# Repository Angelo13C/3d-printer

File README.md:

# 3D printer

https://github.com/user-attachments/assets/5a46b2cb-1782-422b-acf3-2e04f320dc16

I have designed and built a CoreXY 3D printer (all the aspects of the machine: the firmware, a control interface to communicate with the firmware, the electronics and the mechanics). And I've decided to make everything open source!

This is a table of contents:

| Name  | Description |
| ------------- | ------------- |
| [Firmware](firmware)  | The software running on the printer, written in Rust  |
| [Electronics](electronics)  | The electrical board on which the firmware runs, designed in KiCad  |
| Mechanics | The mechanical structure of the printer, designed in Fusion360 (I have not made these files open source yet) |
| [Control interface](control-interface) | An app used to communicate with the firmware of the printer from a desktop computer |

## How it works
[Here I've made a simplified explanation of how a 3D printer works](HOW_A_3D_PRINTER_WORKS.md).

## Contributions
I would be really glad if you could give me some tips on how to improve this project (make a pull request!)

_By the way, I am not a native English speaker. I am sorry if there is any grammar error 😅_

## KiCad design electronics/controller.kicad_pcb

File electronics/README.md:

# Electronics
This is the electrical control board on which the firmware runs.

The board receives stable `24V` from an external power supply unit and requires around `16A` of current at peak, but during almost all of the time it requires around `10A`
of current (because the heaters are not fully on after having reached the target temperature).

On the board there's a switching regulator that converts the `24V` to `5V`, which is used by the `endstops`, the `BLTouch` and by the linear regulator
that instead converts the `5V` to `3.3V` which is used by the [ESP32-S3-WROOM-1](https://www.espressif.com/sites/default/files/documentation/esp32-s3-wroom-1_wroom-1u_datasheet_en.pdf)
microcontroller, the [MT29F2G01ABAGDWB-IT](https://datasheet.lcsc.com/lcsc/1912111437_Micron-Tech-MT29F2G01ABAGDWB-IT-G_C410863.pdf) NAND flash memory.

## Schematic
This is the electrical schematic of the board:

## PCB
The PCB has 4 layers (PWR/SIGNAL, GND, GND, PWR/SIGNAL), this is an image of the top layer:

## Possible improvements
Some ideas for further improvement are:
- Add some little LEDs on the board to show that the power rails are good.
- Use an external Sigma-Delta ADC to improve the accuracy of the temperatures' readings (or calibrate the microcontroller's internal ADC).
- Put the antenna area of the ESP32 on the border of the PCB, to improve the antenna's performance.
- Change some connectors.

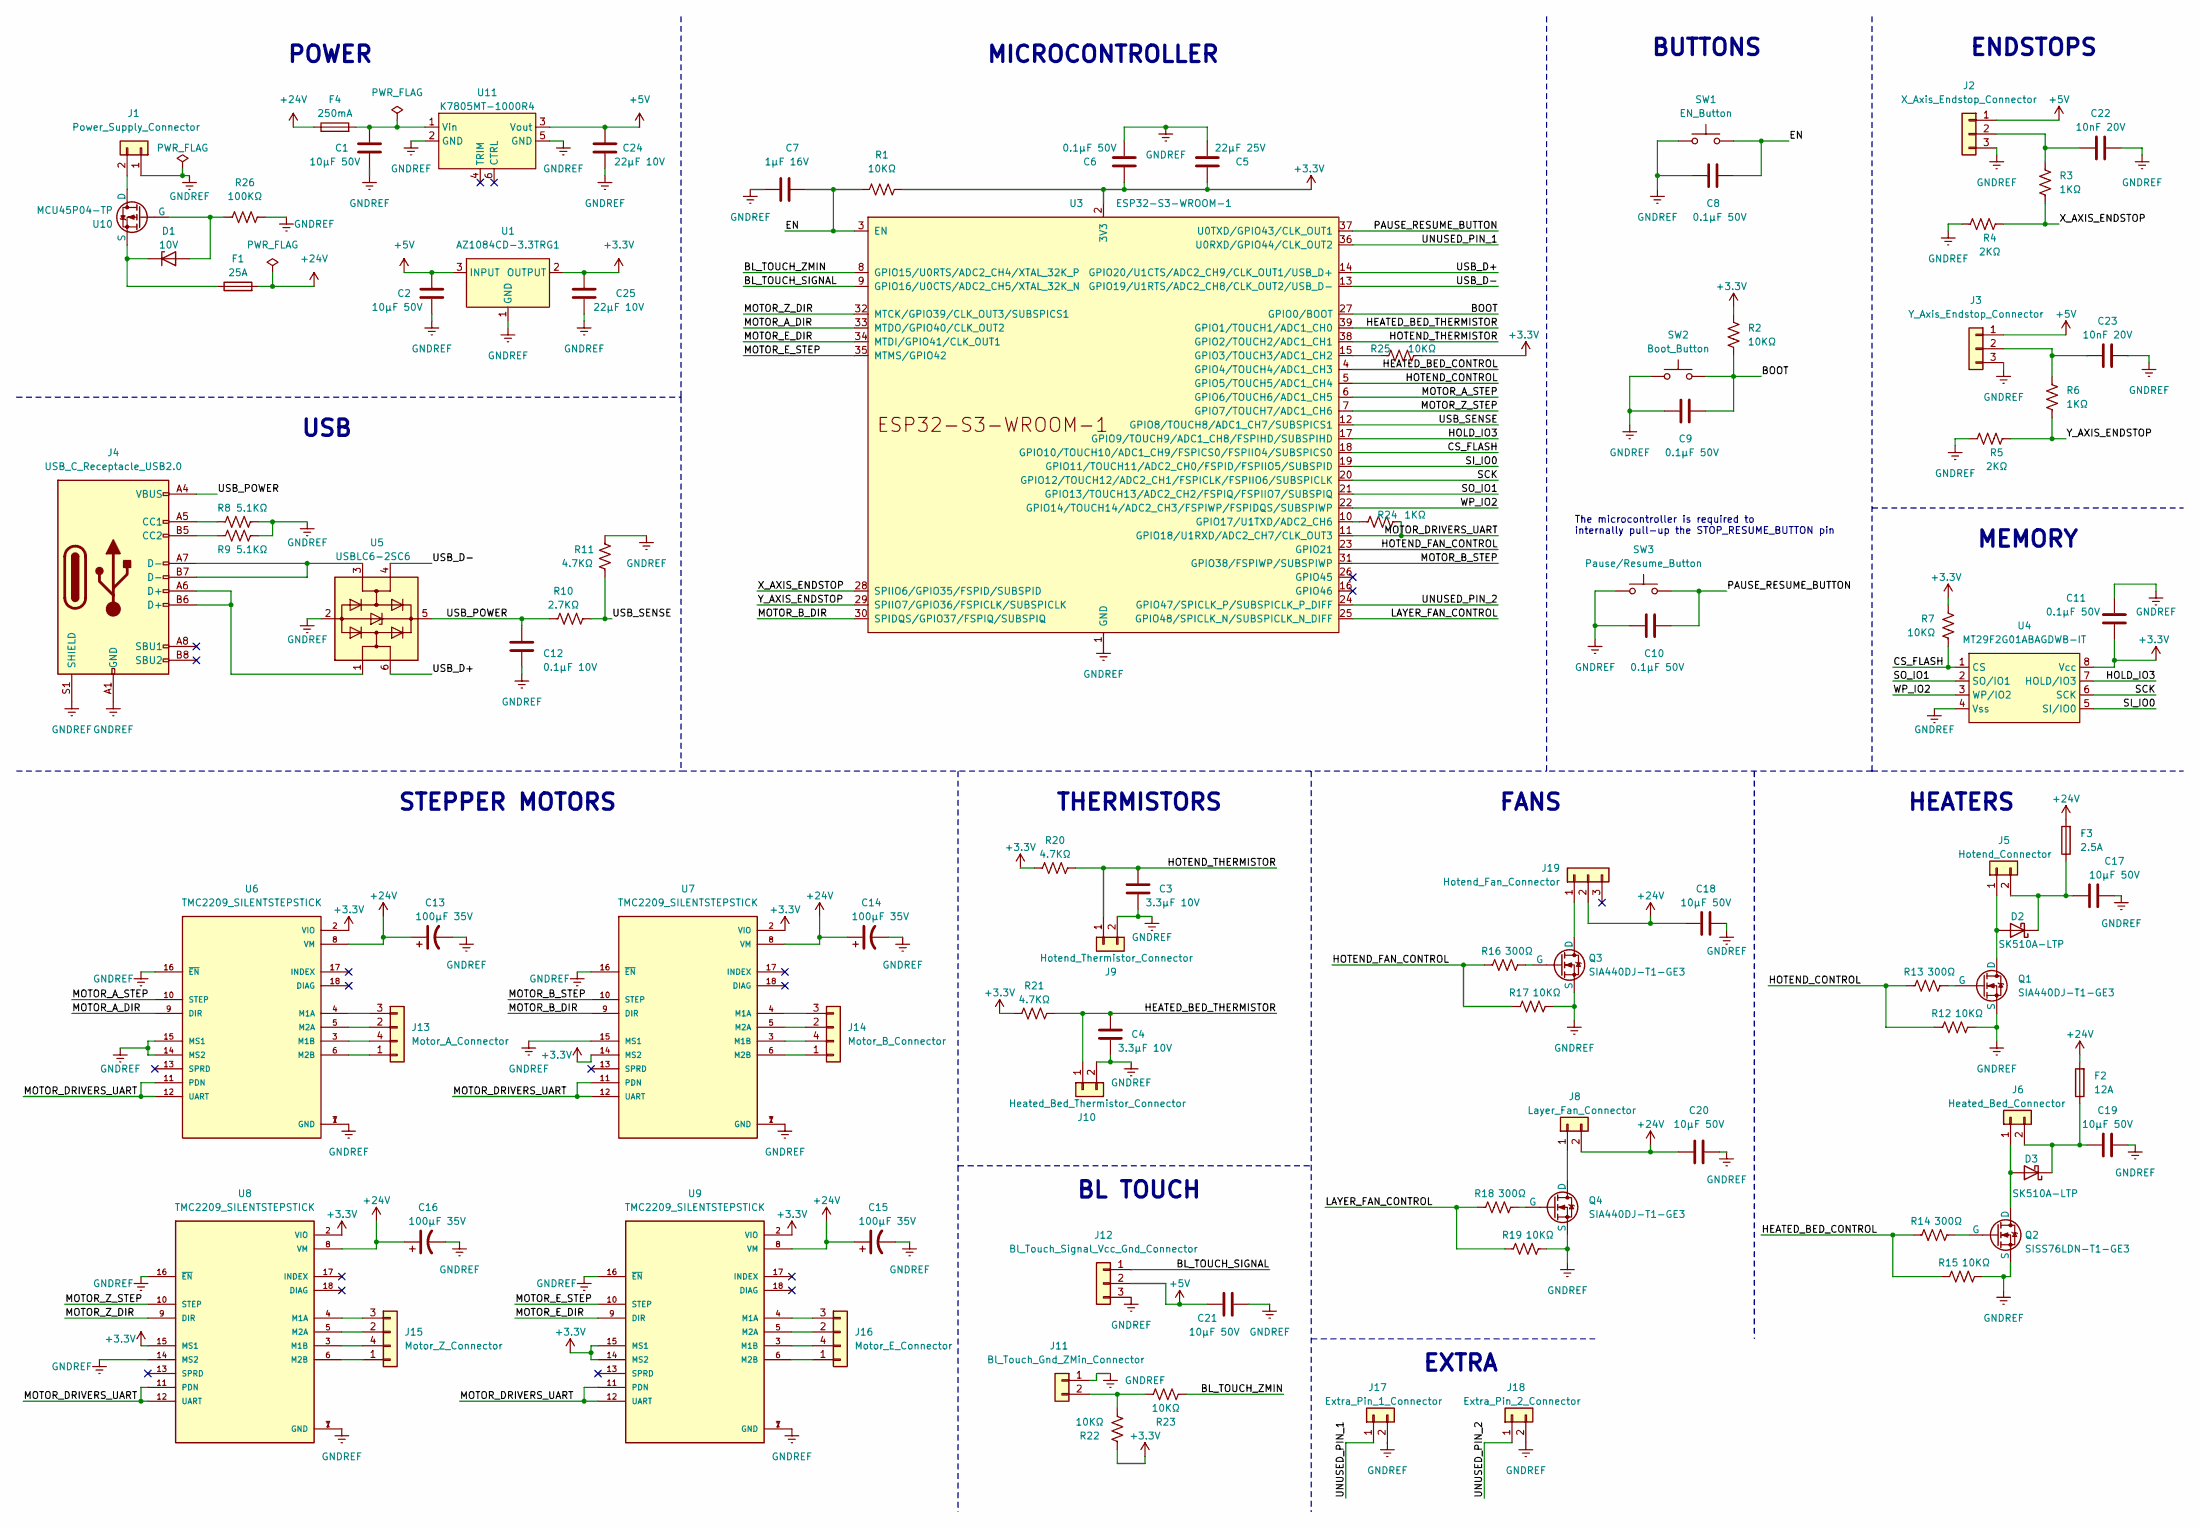
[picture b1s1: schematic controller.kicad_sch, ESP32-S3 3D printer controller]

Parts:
C1, C2, C17, C18, C19, C20, C21: 10µF 50V; C_1206_3216Metric_Pad1.33x1.80mm_HandSolder
C3, C4: 3.3µF 10V; C_1206_3216Metric_Pad1.33x1.80mm_HandSolder
C5: 22µF 25V; C_1206_3216Metric_Pad1.33x1.80mm_HandSolder
C6, C8, C9, C10, C11: 0.1µF 50V; C_1206_3216Metric_Pad1.33x1.80mm_HandSolder
C7: 1µF 16V; C_1206_3216Metric_Pad1.33x1.80mm_HandSolder
C12: 0.1µF 10V; C_1206_3216Metric_Pad1.33x1.80mm_HandSolder
C13, C14, C15, C16: 100µF 35V; CP_Radial_D6.3mm_P2.50mm
C22, C23: 10nF 20V; C_1206_3216Metric_Pad1.33x1.80mm_HandSolder
C24, C25: 22µF 10V; C_1206_3216Metric_Pad1.33x1.80mm_HandSolder
D1: 10V; D_SOD-123
D2, D3: SK510A-LTP; SMADO-214AC_LEAD-FRAME_MCC-L
F1: 25A; Fuse_1206_3216Metric_Pad1.42x1.75mm_HandSolder
F2: 12A; Fuse_1206_3216Metric_Pad1.42x1.75mm_HandSolder
F3: 2.5A; Fuse_1206_3216Metric_Pad1.42x1.75mm_HandSolder
F4: 250mA; Fuse_1206_3216Metric_Pad1.42x1.75mm_HandSolder
J1: Power_Supply_Connector; TerminalBlock_Phoenix_MKDS-1,5-2-5.08_1x02_P5.08mm_Horizont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
J2: X_Axis_Endstop_Connector; PinHeader_1x03_P2.54mm_Vertical
J3: Y_Axis_Endstop_Connector; PinHeader_1x03_P2.54mm_Vertical
J4: USB_C_Receptacle_USB2.0; USB_C_Receptacle_GCT_USB4105-xx-A_16P_TopMnt_Horizontal
J5: Hotend_Connector; SolderWire-0.5sqmm_1x02_P4.6mm_D0.9mm_OD2.1mm
J6: Heated_Bed_Connector; SolderWire-2.5sqmm_1x02_P7.2mm_D2.4mm_OD3.6mm
J8: Layer_Fan_Connector; SolderWire-0.5sqmm_1x02_P4.6mm_D0.9mm_OD2.1mm
J9: Hotend_Thermistor_Connector; JST_XH_B2B-XH-A_1x02_P2.50mm_Vertical
J10: Heated_Bed_Thermistor_Connector; JST_XH_B2B-XH-A_1x02_P2.50mm_Vertical
J11: Bl_Touch_Gnd_ZMin_Connector; PinHeader_1x02_P2.54mm_Vertical
J12: Bl_Touch_Signal_Vcc_Gnd_Connector; PinHeader_1x03_P2.54mm_Vertical
J13: Motor_A_Connector; JST_XH_B4B-XH-A_1x04_P2.50mm_Vertical
J14: Motor_B_Connector; JST_XH_B4B-XH-A_1x04_P2.50mm_Vertical
J15: Motor_Z_Connector; JST_XH_B4B-XH-A_1x04_P2.50mm_Vertical
J16: Motor_E_Connector; JST_XH_B4B-XH-A_1x04_P2.50mm_Vertical
J17: Extra_Pin_1_Connector; SolderWire-0.5sqmm_1x02_P4.6mm_D0.9mm_OD2.1mm
J18: Extra_Pin_2_Connector; SolderWire-0.5sqmm_1x02_P4.6mm_D0.9mm_OD2.1mm
J19: Hotend_Fan_Connector; Molex_KK-254_AE-6410-03A_1x03_P2.54mm_Vertical
Q1, Q3, Q4: SIA440DJ-T1-GE3; Vishay_PowerPAK_SC70-6L_Single
Q2: SISS76LDN-T1-GE3; PowerPAK® 1212-8SH
R1, R2, R7, R12, R15, R17, R19, R22, R23, R25: 10KΩ; R_1206_3216Metric_Pad1.30x1.75mm_HandSolder
R3, R6, R24: 1KΩ; R_1206_3216Metric_Pad1.30x1.75mm_HandSolder
R4, R5: 2KΩ; R_1206_3216Metric_Pad1.30x1.75mm_HandSolder
R8, R9: 5.1KΩ; R_1206_3216Metric_Pad1.30x1.75mm_HandSolder
R10: 2.7KΩ; R_1206_3216Metric_Pad1.30x1.75mm_HandSolder
R11, R20, R21: 4.7KΩ; R_1206_3216Metric_Pad1.30x1.75mm_HandSolder
R13, R14, R16, R18: 300Ω; R_1206_3216Metric_Pad1.30x1.75mm_HandSolder
R26: 100KΩ; R_1206_3216Metric_Pad1.30x1.75mm_HandSolder
SW1: EN_Button; SW_PUSH_6mm
SW2: Boot_Button; SW_PUSH_6mm
SW3: Pause/Resume_Button; SolderWire-0.5sqmm_1x02_P4.6mm_D0.9mm_OD2.1mm
U1: AZ1084CD-3.3TRG1; TO-252-3_TabPin2
U3: ESP32-S3-WROOM-1
U4: MT29F2G01ABAGDWB-IT; U-PDFN (MLP8)
U5: USBLC6-2SC6; SOT-23-6
U6, U7, U8, U9: TMC2209_SILENTSTEPSTICK; MODULE_TMC2209_SILENTSTEPSTICK; PARTREV 1.20
U10: MCU45P04-TP; TO-252-3_TabPin2
U11: K7805MT-1000R4; MODULE_6-SMD

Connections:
+3.3V: C5.1, C6.1, C11.1, C25.2, R1.2, R2.2, R7.2, R20.1, R21.1, R22.1, R25.2, U1.2 (OUTPUT), U3.2 (3V3), U4.8 (Vcc), U6.2 (VIO), U7.2 (VIO), U7.14 (MS2), U8.2 (VIO), U8.15 (MS1), U9.2 (VIO), U9.14 (MS2), U9.15 (MS1)
+5V: C2.2, C21.1, C24.2, J2.1, J3.1, J12.2, U1.3 (INPUT), U11.3 (Vout)
+24V: C13.1, C14.1, C15.1, C16.1, C18.2, C20.1, F1.2, F2.2, F3.2, F4.1, J8.2, J19.2, U6.8 (VM), U7.8 (VM), U8.8 (VM), U9.8 (VM)
/BL_TOUCH_SIGNAL: J12.1, U3.9 (GPIO16/U0CTS/ADC2_CH5/XTAL_32K_N)
/BL_TOUCH_ZMIN: R23.1, U3.8 (GPIO15/U0RTS/ADC2_CH4/XTAL_32K_P)
/BOOT: C9.1, R2.1, SW2.2, U3.27 (GPIO0/BOOT); also elsewhere on the board
/CS_FLASH: R7.1, U3.18 (GPIO10/TOUCH10/ADC1_CH9/FSPICS0/FSPIIO4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), U4.1 (CS)
/EN: C7.1, C8.1, R1.1, SW1.2, U3.3 (EN); also elsewhere on the board
/HEATED_BED_CONTROL: R14.1, R15.1, U3.4 (GPIO4/TOUCH4/ADC1_CH3)
/HEATED_BED_THERMISTOR: C4.2, J10.1, R21.2, U3.39 (GPIO1/TOUCH1/ADC1_CH0)
/HOLD_IO3: U3.17 (GPIO9/TOUCH9/ADC1_CH8/FSPIHD/SUBSPIHD), U4.7 (HOLD/IO3)
/HOTEND_CONTROL: R12.1, R13.1, U3.5 (GPIO5/TOUCH5/ADC1_CH4)
/HOTEND_FAN_CONTROL: R16.1, R17.1, U3.23 (GPIO21)
/HOTEND_THERMISTOR: C3.2, J9.1, R20.2, U3.38 (GPIO2/TOUCH2/ADC1_CH1)
/LAYER_FAN_CONTROL: R18.1, R19.1, U3.25 (GPIO48/SPICLK_N/SUBSPICLK_N_DIFF)
/MOTOR_A_DIR: U3.33 (MTDO/GPIO40/CLK_OUT2), U6.9 (DIR)
/MOTOR_A_STEP: U3.6 (GPIO6/TOUCH6/ADC1_CH5), U6.10 (STEP)
/MOTOR_B_DIR: U3.30 (SPIDQS/GPIO37/FSPIQ/SUBSPIQ), U7.9 (DIR)
/MOTOR_B_STEP: U3.31 (GPIO38/FSPIWP/SUBSPIWP), U7.10 (STEP)
/MOTOR_DRIVERS_UART: R24.2, U3.11 (GPIO18/U1RXD/ADC2_CH7/CLK_OUT3), U6.11 (PDN), U6.12 (UART), U7.11 (PDN), U7.12 (UART), U8.11 (PDN), U8.12 (UART), U9.11 (PDN), U9.12 (UART)
/MOTOR_E_DIR: U3.34 (MTDI/GPIO41/CLK_OUT1), U9.9 (DIR)
/MOTOR_E_STEP: U3.35 (MTMS/GPIO42), U9.10 (STEP)
/MOTOR_Z_DIR: U3.32 (MTCK/GPIO39/CLK_OUT3/SUBSPICS1), U8.9 (DIR)
/MOTOR_Z_STEP: U3.7 (GPIO7/TOUCH7/ADC1_CH6), U8.10 (STEP)
/PAUSE_RESUME_BUTTON: C10.1, SW3.2, U3.37 (U0TXD/GPIO43/CLK_OUT1)
/SCK: U3.20 (GPIO12/TOUCH12/ADC2_CH1/FSPICLK/FSPIIO6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), U4.6 (SCK)
/SI_IO0: U3.19 (GPIO11/TOUCH11/ADC2_CH0/FSPID/FSPIIO5/S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), U4.5 (SI/IO0)
/SO_IO1: U3.21 (GPIO13/TOUCH13/ADC2_CH2/FSPIQ/FSPIIO7/S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), U4.2 (SO/IO1)
/UNUSED_PIN_1: J17.1, U3.36 (U0RXD/GPIO44/CLK_OUT2)
/UNUSED_PIN_2: J18.1, U3.24 (GPIO47/SPICLK_P/SUBSPICLK_P_DIFF)
/USB_D+: U3.14 (GPIO20/U1CTS/ADC2_CH9/CLK_OUT1/USB_D+), U5.6 (I/O1)
/USB_D-: U3.13 (GPIO19/U1RTS/ADC2_CH8/CLK_OUT2/USB_D-), U5.4 (I/O2)
/USB_POWER: C12.1, J4.A4 (VBUS), J4.A9 (VBUS), J4.B4 (VBUS), J4.B9 (VBUS), R10.2, U5.5 (VBUS)
/USB_SENSE: R10.1, R11.2, U3.12 (GPIO8/TOUCH8/ADC1_CH7/SUBSPICS1)
/WP_IO2: U3.22 (GPIO14/TOUCH14/ADC2_CH3/FSPIWP/FSPIDQS/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), U4.3 (WP/IO2)
/X_AXIS_ENDSTOP: R3.1, R4.1, U3.28 (SPIIO6/GPIO35/FSPID/SUBSPID)
/Y_AXIS_ENDSTOP: R5.1, R6.1, U3.29 (SPIIO7/GPIO36/FSPICLK/SUBSPICLK)
GNDREF: C1.1, C2.1, C3.1, C4.1, C5.2, C6.2, C7.2, C8.2, C9.2, C10.2, C11.2, C12.2, C13.2, C14.2, C15.2, C16.2, C17.2, C18.1, C19.2, C20.2, C21.2, C22.2, C23.2, C24.1, C25.1, J1.1, J2.3, J3.3, J4.A1 (GND), J4.A12 (GND), J4.B1 (GND), J4.B12 (GND), J4.S1 (SHIELD), J9.2, J10.2, J11.1, J12.3, J17.2, J18.2, Q1.3 (S), Q2.3 (S), Q3.3 (S), Q4.3 (S), R4.2, R5.2, R8.2, R9.2, R11.1, R12.2, R15.2, R17.2, R19.2, R26.2, SW1.1, SW2.1, SW3.1, U1.1 (GND), U3.1 (GND), U3.40 (GND), U3.41 (GND), U4.4 (Vss), U5.2 (GND), U6.1 (GND), U6.7 (GND), U6.14 (MS2), U6.15 (MS1), U6.16 (~EN), U7.1 (GND), U7.7 (GND), U7.15 (MS1), U7.16 (~EN), U8.1 (GND), U8.7 (GND), U8.14 (MS2), U8.16 (~EN), U9.1 (GND), U9.7 (GND), U9.16 (~EN), U11.2 (GND), U11.5 (GND); also elsewhere on the board
unnamed: D1.2 (A), R26.1, U10.1 (G)
unnamed: D1.1 (K), F1.1, U10.3 (S)
unnamed: D2.2 (A), J5.1, Q1.1 (D)
unnamed: C17.1, D2.1 (K), F3.1, J5.2
unnamed: D3.2 (A), J6.1, Q2.1 (D)
unnamed: C19.1, D3.1 (K), F2.1, J6.2
unnamed: J1.2, U10.2 (D)
unnamed: C22.1, J2.2, R3.2
unnamed: C23.1, J3.2, R6.2
unnamed: J4.A5 (CC1), R8.1
unnamed: J4.B5 (CC2), R9.1
unnamed: J4.A6 (D+), J4.B6 (D+), U5.1 (I/O1)
unnamed: J4.A7 (D-), J4.B7 (D-), U5.3 (I/O2)
unnamed: J8.1, Q4.1 (D)
unnamed: J11.2, R22.2, R23.2
unnamed: J13.1, U6.6 (M2B)
unnamed: J13.2, U6.5 (M2A)
unnamed: J13.3, U6.4 (M1A)
unnamed: J13.4, U6.3 (M1B)
unnamed: J14.1, U7.6 (M2B)
unnamed: J14.2, U7.5 (M2A)
unnamed: J14.3, U7.4 (M1A)
unnamed: J14.4, U7.3 (M1B)
unnamed: J15.1, U8.6 (M2B)
unnamed: J15.2, U8.5 (M2A)
unnamed: J15.3, U8.4 (M1A)
unnamed: J15.4, U8.3 (M1B)
unnamed: J16.1, U9.6 (M2B)
unnamed: J16.2, U9.5 (M2A)
unnamed: J16.3, U9.4 (M1A)
unnamed: J16.4, U9.3 (M1B)
unnamed: J19.1, Q3.1 (D)
unnamed: Q1.2 (G), R13.2
unnamed: Q2.2 (G), R14.2
unnamed: Q3.2 (G), R16.2
unnamed: Q4.2 (G), R18.2
unnamed: R25.1, U3.15 (GPIO3/TOUCH3/ADC1_CH2)
unnamed: R24.1, U3.10 (GPIO17/U1TXD/ADC2_CH6)
unnamed: C1.2, F4.2, U11.1 (Vin)

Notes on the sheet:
FANS
BL TOUCH
USB
STEPPER MOTORS
The microcontroller is required to internally pull-up the STOP_RESUME_BUTTON pin
MICROCONTROLLER
EXTRA
ENDSTOPS
HEATERS
BUTTONS
MEMORY
THERMISTORS
POWER

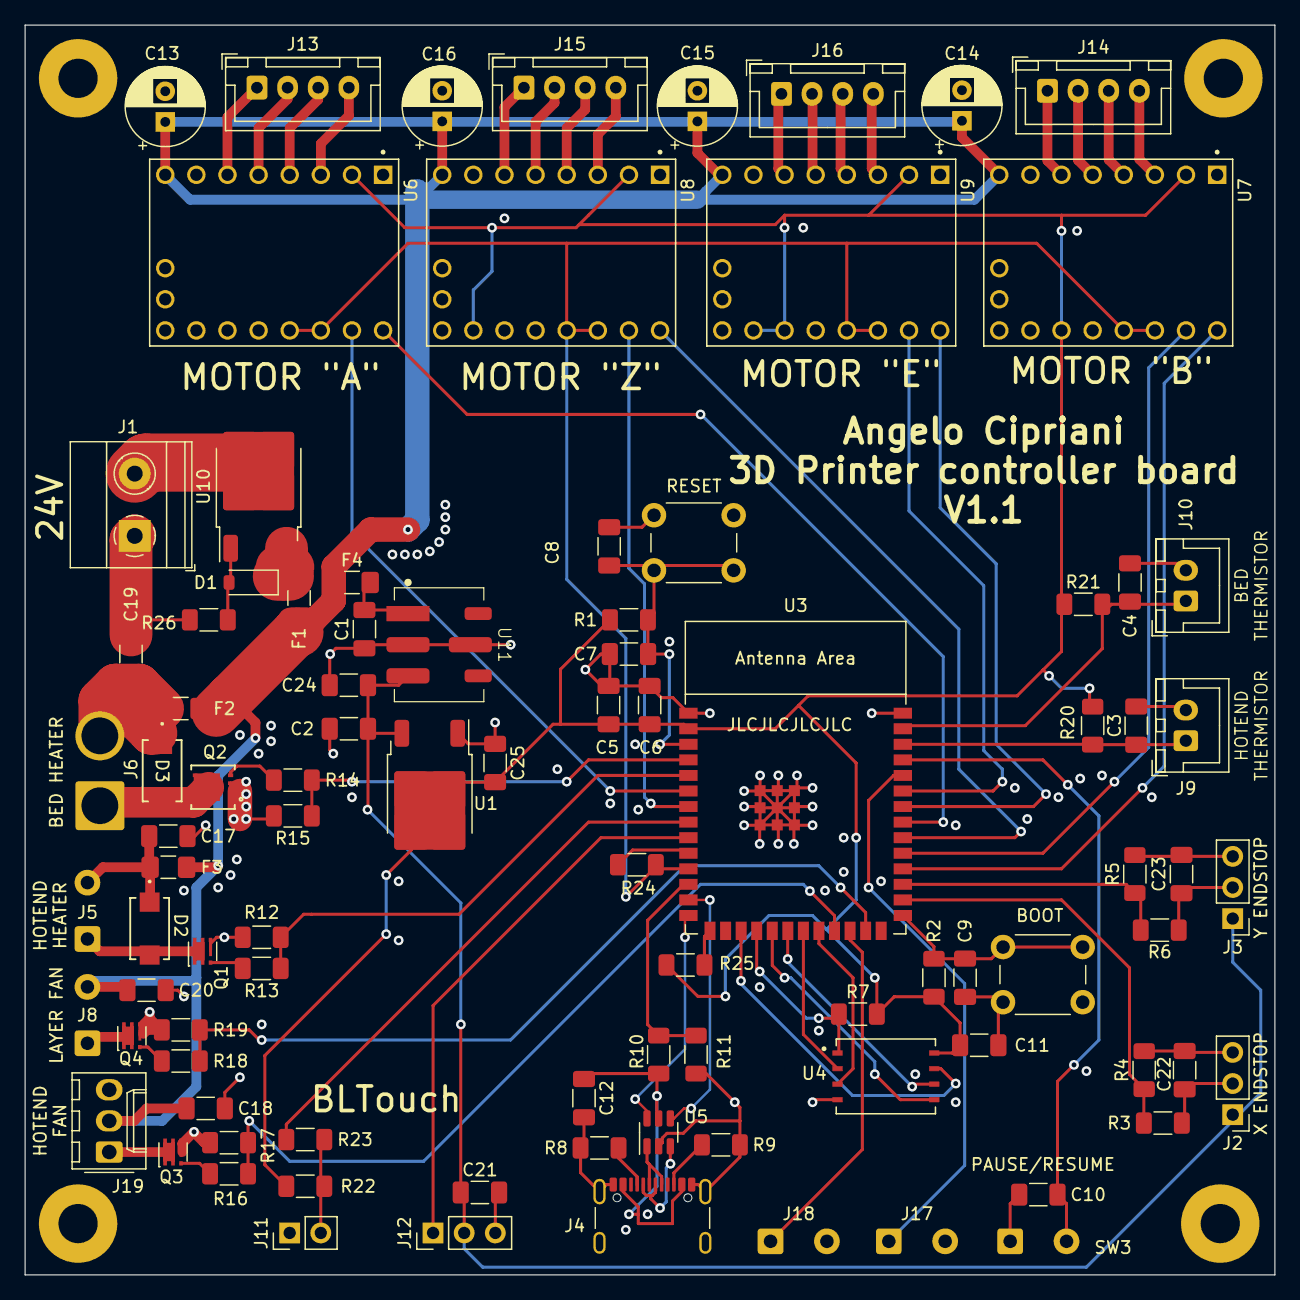
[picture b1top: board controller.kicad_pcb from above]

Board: 4 copper layers, 102.0 x 102.0 mm, 93 parts (0 on the bottom side), 77 nets.

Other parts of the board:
BOOT: Boot_Button; SW_PUSH_6mm
RESET: EN_Button; SW_PUSH_6mm

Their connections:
/BOOT: BOOT.2; also elsewhere on the board
/EN: RESET.2; also elsewhere on the board
GNDREF: BOOT.1, RESET.1; also elsewhere on the board

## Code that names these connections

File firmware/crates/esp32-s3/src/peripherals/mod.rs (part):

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	bed_thermistor_pin: Option<<Self as PeripheralsTrait>::HeatedBedAdcPin>,

	hotend_cartridge_heater_pin: Option<<Self as PeripheralsTrait>::CartridgeHeaterPin>,
	hotend_thermistor_pin: Option<<Self as PeripheralsTrait>::HotendAdcPin>,

	adc: Option<<Self as PeripheralsTrait>::Adc>,

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	type StepperTickerTimer = Timer;
	type Kinematics = CoreXYKinematics;

	type LeftDirPin = PinDriver<'static, Gpio40, Output>;
	type LeftStepPin = PinDriver<'static, Gpio6, Output>;
	type RightDirPin = PinDriver<'static, Gpio37, Output>;
	type RightStepPin = PinDriver<'static, Gpio38, Output>;
	type ZAxisDirPin = PinDriver<'static, Gpio39, Output>;
	type ZAxisStepPin = PinDriver<'static, Gpio7, Output>;
	type ExtruderDirPin = PinDriver<'static, Gpio41, Output>;
	type ExtruderStepPin = PinDriver<'static, Gpio42, Output>;

	type UartDriver = UARTDriver<'static>;

	type XAxisEndstop = Button<InputPin<'static, Gpio35>>;
	type YAxisEndstop = Button<InputPin<'static, Gpio36>>;
	type ZAxisEndstop = BLTouch<LedcPwmPin<'static>, InputPin<'static, Gpio15>>;

	type FlashChip = MT29F2G01ABAGDWB;
	type FlashSpi = SpiSingleDeviceDriver<'static>;
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	type FanPin = LedcPwmPin<'static>;

	type CartridgeHeaterPin = LedcPwmPin<'static>;
	type HotendAdcPin = AdcPin<'static, ADC1, 3, Gpio2>;

	type HeatedBedHeaterPin = LedcPwmPin<'static>;
	type HeatedBedAdcPin = AdcPin<'static, ADC1, 3, Gpio1>;

	type Adc = Adc<'static, ADC1>;

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	type Ota = EspOta;

	#[cfg(feature = "usb")]
	type UsbSensePin = InputPin<'static, Gpio20>;
	#[cfg(feature = "usb")]
	type UsbBus = firmware_core::printer::components::mock::MockUsbBus;

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
	fn take_hotend_thermistor_pin(&mut self) -> Option<Self::HotendAdcPin>
	{
		self.hotend_thermistor_pin.take()
	}

	fn take_adc(&mut self) -> Option<Self::Adc>
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			system_time: Some(SystemTime::new()?),
			uart_driver: Some(UARTDriver(UartDriver::new(
				peripherals.uart1,
				peripherals.pins.gpio18,
				peripherals.pins.gpio17,
				None as Option<Gpio0>,
				None as Option<Gpio0>,
				&crate::config::components::UART_CONFIGURATION,
			)?)),
			stepper_ticker_timer: Some(Timer::new(
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				&crate::config::components::STEPPER_TIMER_CONFIG,
			)?),
			kinematics: CoreXYKinematics,
			left_motor_dir_pin: Some(PinDriver::output(peripherals.pins.gpio40)?),
			left_motor_step_pin: Some(PinDriver::output(peripherals.pins.gpio6)?),
			right_motor_dir_pin: Some(PinDriver::output(peripherals.pins.gpio37)?),
			right_motor_step_pin: Some(PinDriver::output(peripherals.pins.gpio38)?),
			z_axis_motor_dir_pin: Some(PinDriver::output(peripherals.pins.gpio39)?),
			z_axis_motor_step_pin: Some(PinDriver::output(peripherals.pins.gpio7)?),
			extruder_motor_dir_pin: Some(PinDriver::output(peripherals.pins.gpio41)?),
			extruder_motor_step_pin: Some(PinDriver::output(peripherals.pins.gpio42)?),
			x_axis_endstop: Some(Button::new(InputPin(PinDriver::input(peripherals.pins.gpio35)?))),
			y_axis_endstop: Some(Button::new(InputPin(PinDriver::input(peripherals.pins.gpio36)?))),
			z_axis_endstop: Some(BLTouch::new(
				LedcPwmPin(LedcDriver::new(
					peripherals.ledc.channel2,
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						peripherals.ledc.timer1,
						&crate::config::components::BL_TOUCH_SIGNAL_PWM_TIMER,
					)?,
					peripherals.pins.gpio16,
				)?),
				InputPin(PinDriver::input(peripherals.pins.gpio15)?),
			)?),
			flash_chip: MT29F2G01ABAGDWB,
			flash_spi: Some(SpiSingleDeviceDriver::new_single(
				peripherals.spi2,
				peripherals.pins.gpio12,
				peripherals.pins.gpio11,
				Some(peripherals.pins.gpio13),
				Some(peripherals.pins.gpio10),
				&FLASH_SPI_DRIVER_CONFIG,
				&FLASH_SPI_CONFIG,
			)?),
			hotend_fan_pin: Some(LedcPwmPin(LedcDriver::new(
				peripherals.ledc.channel1,
				&fans_timer_driver,
				peripherals.pins.gpio21,
			)?)),
			layer_fan_pin: Some(LedcPwmPin(LedcDriver::new(
				peripherals.ledc.channel0,
				&fans_timer_driver,
				peripherals.pins.gpio48,
			)?)),
			bed_cartridge_heater_pin: Some(LedcPwmPin(LedcDriver::new(
				peripherals.ledc.channel4,
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					peripherals.ledc.timer2,
					&crate::config::components::BED_HEATER_PWM_TIMER,
				)?,
				peripherals.pins.gpio4,
			)?)),
			bed_thermistor_pin: Some(AdcPin::new(AdcChannelDriver::new(peripherals.pins.gpio1)?)),
			hotend_cartridge_heater_pin: Some(LedcPwmPin(LedcDriver::new(
				peripherals.ledc.channel6,
				&LedcTimerDriver::new(
					peripherals.ledc.timer3,
					&crate::config::components::HOTEND_HEATER_PWM_TIMER,
				)?,
				peripherals.pins.gpio5,
			)?)),
			hotend_thermistor_pin: Some(AdcPin::new(AdcChannelDriver::new(peripherals.pins.gpio2)?)),
			adc: Some(Adc(AdcDriver::new(peripherals.adc1, &ADC_CONFIG)?)),
			wifi: Some(AsyncWifi::wrap(
				EspWifi::wrap(WifiDriver::new(peripherals.modem, sys_loop.clone(), Some(nvs))?)?,
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
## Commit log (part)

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2023-10-22 ✨ Add HTTPs client in control-interface
2023-10-22 🚧 Add FileList functionality in control-interface
2023-10-22 💄 Improve menu selection in control-interface
2023-10-22 🐛 Update empty file list message immediately in control-interface
2023-10-23 🔧 Change build settings in control-interface
2023-10-23 🚧 Add SettingsFieldsDisplay basic functionality in control-interface
2023-10-23 🐛 Fix child out of bounds error in control-interface
2023-10-24 🍱 Change the footprint of TO-253-3_TabPin2 in KiCad
2023-10-26 ✨ Add PID gains in the settings of control-interface
2023-10-28 ✨ Add print status functionality in control-interface
2023-10-28 🍱 Add texture of the temperature graph background in control-interface
2023-10-28 🔧 Update SVGImporter preset in control-interface
2023-10-28 🐛 Add some RequestType variants in control-interface
2023-10-30 📝 Remove empty Alarm mode section in the documentation of the BLTouch struct
2023-10-30 ✨ Implement the Default trait for VectorN
2023-11-02 ✨ Add utilities to use G-code parameters
2023-11-02 ✨ Implement Debug for the ReadPercentageError struct
2023-11-02 ✨ Add the most important G-code commands
    For now the supported commands are: G0, G1, G20, G21, G28, G60 (doesn't work yet), G61, G90, G91, G92, M82, M83, M104, M106, M107, M109, M140, M190
2023-11-02 🚚 Move/rename some structs
2023-11-02 ♻️ Implement the Default trait manually for the GCodeExecuter struct
2023-11-02 ✨ Implement the Debug trait for various errors
2023-11-02 ✨ Add some associated types to the Peripherals trait
2023-11-03 ✨ Update ComponentsConfig and the tick methods of Printer3D and Printer3DComponents
2023-11-04 ⬆️ Upgrade embedded-hal dependency to 1.0.0-rc.1
2023-11-04 🤡 Mock UART
2023-11-04 ✨ Make callbacks of interrupts implement Send
2023-11-04 ✨ Make types that are required in ISR implement Send
2023-11-04 ✨ Add missing methods in the Peripherals trait
2023-11-05 ➕ Add enumset dependency to firmware-esp32-s3
2023-11-06 🚩 Add "alloc" and "nightly" features to the default ones in firmware-esp32-s3
2023-11-06 ➕ Add embedded-svc dependency to firmware-core
2023-11-06 ➕ Add strum dependency to firmware-core
2023-11-06 ✅ Fix compiler error in a test
2023-11-06 🚧 Add possibility for the Communication thread to send commands to be executed in the Components thread
2023-11-06 ✨ Add the Resources struct for processing data in http callbacks
2023-11-06 ✨ Add the HttpServer trait
2023-11-06 🚩 Add usb feature in firmware-core
2023-11-07 ✨ Add the possibility to get the file being printed by the PrintProcess struct
2023-11-08 ✨ Add GCodeHistory functionality
2023-11-08 ✏️ Fix typo in documentation
2023-11-08 ✨ Add the possibility to know the start time and estimated duration of a print from PrintProcess
2023-11-08 ⚡️ Make the command_buffer of the GCodeExecuter a VecDeque instead of a Vec
2023-11-08 📝 Add documentation to some parts of GCodeExecuter
2023-11-08 ✨ Make SystemTime cloneable in firmware-esp32-s3
2023-11-13 ➕ Add serde dependency to firmware-core
2023-11-14 ✨ Add the possibility to take a "screenshot" of the printer's state
2023-11-14 ✨ Add the Communicator trait
2023-11-14 ✨ Require SystemTime in the Peripherals trait to be Sendable
2023-11-15 ✨ Add possibility for the Communication thread to know how many G-code commands are in the buffer
2023-11-15 🚨 Remove unused imports
2023-11-15 ✨ Add some basic security functionality to the communications
2023-11-15 🤡 Mock UsbBus
2023-11-15 ✨ Declare the sub-modules of communication
2023-11-15 ✨ Add USB communicator
2023-11-15 ✨ Add communication's associated types to the Peripherals trait
2023-11-15 ✨ Add the Communication struct
2023-11-15 🔧 Add the configuration files for the communication part of firmware-esp32-s3
2023-11-17 🚧 Implement some HTTP callbacks
2023-11-17 💚 Set the environment variables to the secrets in GitHub actions
    https://docs.github.com/en/actions/security-guides/using-secrets-in-github-actions#using-secrets-in-a-workflow
2023-11-18 ✨ Add a panic handler
2023-11-20 🐛 Fix the assert in datagram_as_bytes_mut of tmc2209
2023-11-20 🤡 Mock WatchdogCreator and Watchdog
2023-11-20 ✨ Make the firmware actually restart the watchdog periodically
2023-11-21 🐛 Fix index out of bounds error in the cycling of pages of the flash memory
2023-11-21 🐛 Make SystemTime::delay use FreeRTOS's delay if it's short enough in firmware-esp32-s3
2023-11-21 ✨ Add the possibility for the firmware to know its IP address
2023-11-22 🐛 Fix the fact that env!("POSSIBLE_PEPPERS") could only have 1 value
    This is done by splitting the possible peppers by a whitespace instead of a newline
2023-11-22 🚑️ Move the components to a new thread instead of the main one to set a custom stack size
2023-11-22 ✨ Add OTA update
2023-11-23 🔊 Add info logs in the HTTP callbacks
2023-11-23 🔊 Improve info logs in HTTP callbacks
2023-11-23 🚸 Improve user experience in OTA updates
2023-11-23 🎉 Begin the firmware-tools project
2023-11-23 ➕ Add reqwest dependency to firmware-tools
2023-11-23 ✨ Add the possibility of saving preferences in firmware-tools
2023-11-23 ✨ Add possibility to not hash the security password
2023-11-23 🔧 Set the cargo runner of firmware-esp32-s3 to `firmware-tools flash`
2023-11-25 🐛 Fix a bug in the formula to convert an ADC sample to a temperature for the NTC thermistor
2023-11-25 🐛 Make the max readable value of the ADC of the esp32-s3 the correct one
2023-11-26 🔧 Increase the stack size of the main task in firmware-esp32-s3
2023-11-26 🐛 Make the Timer used for StepperTicker actually start working when enabled in firmware-esp32-s3
2023-11-26 🐛 Fix errors being printed by the esp32-s3 when panicking
2023-11-27 ✨ Initialize the flash memory chip at the creation of the file system
2023-11-27 🐛 Fix the byte order of a column address
2023-11-27 🐛 Make partial programs of the SPI flash memory possible
    ProgramLoad (as stated in the datasheet) cleared all the bytes to 0xFF, so for partial programs of a page with this command would clear to 0xFF the not overwritten values (it's actually weird). Progr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
2023-11-28 🐛 Fix erase_blocks not being able to erase more than 1 block at a time
    The BlockErase command cleared also the WEL bit (the WriteEnable bit) and so after the first BlockErase command was issued, the other ones wouldn't take effect
2023-11-28 🧑‍💻 Implement Debug for some errors
2023-11-28 ✨ Implement the send-file HTTP callback
2023-11-28 🐛 Fix SpiFlashMemory::program not being able to program more than 1 page at a time
    The Program command cleared also the WEL bit (the WriteEnable bit) and so after the first Program command was issued, the other ones wouldn't take effect
2023-11-29 🐛 Make PrintProcess::tick() remember the correct lines it parsed when one line contains an error
    Previously in PrintProcess::tick if a line couldn't be parsed, the PrintProcess would "forget" all the lines that were correctly parsed (even the last one that could be only read by half), introducin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
2023-11-29 🐛 Remove the semicolon at the start of a parsed comment
2023-11-29 🧑‍💻 Implement the Debug trait for the planner's Block and its Flags
2023-11-29 🧑‍💻 Improve the debug format of the Distance struct
2023-11-29 ✅ Fix a test that failed for compile errors
2023-12-02 🍱 Fix some inverted pins in the PowerPAK_SC70-6L_Single footprint
2023-12-06 🚧 Working on a way to move the tool's head from the control-interface
2023-12-06 💄 Decrease the size of a block of settings
2023-12-06 🚧 Working on a way to connect the control-interface to the firmware through WiFi
2023-12-06 💄 Update the Unity scene with all the necessary elements in control-interface
2023-12-06 💄 Update the background of some symbols in the electronics schematic
2023-12-07 📝 Add a README file to firmware
2023-12-07 📝 Update the explanation of how a 3D printer works
2023-12-09 📝 Add a README file to the repository
2023-12-10 🐛 Fix the footprints of the PMOS in KiCad
2023-12-10 🔖 Set the revision of the schematic to 1.1 in KiCad
2023-12-10 ✨ Add a way to use the Timer trait directly with ticks instead of durations
2023-12-10 🤡 Mock the methods that use ticks of the Timer
2023-12-10 📝 Push the firmware_core documentation to GitHub
2023-12-10 📝 Add some status badges to the README file of the firmware
2023-12-11 📝 Update the documentation in the GitHub pages
2024-03-15 ✨ Add the possibility to set the reply delay of the TMC2209 driver
2024-03-15 🐛 Fix other bugs in the motion planner
2024-03-15 🧑‍💻 Implement the Debug trait for ReadRegisterError of a TMC2209
2024-03-15 🐛 Make the module that contains TMC2209's registers public
2024-03-23 💚 Import the Debug trait
2024-03-23 🏷️ Make the RotationalDirection::from_sign take an int instead of a float
2024-03-23 🐛 Fix the broken motion planner
2024-03-23 👥 Give credits to the Marlin project
2024-03-23 ✨ Make the GCodeExecuter prepare all the "preparable" commands in a single tick
2024-03-23 🔧 Add the ESP_IDF_SYS_ROOT_CRATE env var in the esp32-s3 .config file
2024-07-11 🔧 Update the sdkconfig.defaults file for esp32-s3
2024-07-14 🐛 Fix a bug in the homing procedure that could occur if the block buffer was full
    Previously if the block buffer was full and the HomingProcedure attempted to plan a block and failed, it would still move on to the next homing move (so if it was homing the X axis, even though the m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
2024-07-14 🐛 Fix some feed rate bugs in GCode execution
2024-07-14 🚧 Setup some things for the bed leveling feature
2024-07-14 🚧 Add most of the bed leveling functionality (it's not finished yet)
2024-07-14 🏷️ Use the core library instead of the std library
2024-07-14 ✨ Add the support for the M105 GCode command
2024-07-14 ✨ Add the REMAINING things for bed leveling
    I forgot to include some code in the previous commit
2024-07-14 🔥 Remove my custom implementation of a Mutex
2024-09-06 🔧 Enable the interrupt watchdog for the firmware_esp32_s3
2024-09-06 🔥 Remove the print_logs_from_isr function call
2024-09-06 🔨 Update the build script
2024-09-06 ✨ Add some functions to the Timer trait
2024-09-07 ✨ Add the set_commands_in_buffer_count function in the print process
2024-09-07 ✨ Disable the TMC drivers when the motion controller is paused
2024-09-07 ✨ Update the Printer3DComponents struct based on the new functionality
2024-09-07 🚨 Return the eventual error given by an initialization function in the TMC2209 struct
2024-09-07 🐛 Fix various bugs in various GCode commands
2024-09-07 ✨ Return a Result from the BedLevelingProcedure::tick function
2024-09-07 🐛 Fix a bug with empty moves in the motion Planner and add the possibility to delay blocks
2024-09-07 ✨ Implement the get_alarm_in_ticks function for the timer of the esp32-s3
2024-10-26 📝 Add documentation to the HttpServer trait
2024-10-26 📝 Add documentation to the http command module
2024-10-26 📝 Add documentation to the communication module
2024-10-26 📝 Update the documentation of the ota module
2024-10-26 📝 Add documentation to the http request module
2024-10-26 📝 Add documentation to the security ip_address module
2024-10-26 📝 Add documentation to the bl_touch driver module
2024-10-26 📝 Add documentation to the cartridge heater driver module
2024-10-26 📝 Add documentation to the drivers module
2024-10-26 📝 Add documentation to the stepper_motor driver module
2024-10-26 📝 Add documentation to the HAL ADC module
2024-10-26 📝 Add documentation to the HAL module
2024-10-26 📝 Add documentation to the HAL timer module
2024-10-26 📝 Add documentation to the HAL watchdog module
2024-10-26 📝 Add documentation to the components module
2024-10-26 📝 Add documentation to the endstop module
2024-10-26 📝 Add documentation to the motion module
2024-10-26 📝 Add documentation to the motion ticker module
2024-10-26 📝 Add documentation to the print_process module
2024-10-26 📝 Update the documentation of the temperature pid module
2024-10-26 📝 Add documentation to the temperature safety module
2024-10-26 📝 Add documentation to the temperature_change module
2024-10-26 📝 Add documentation to the printer module
2024-10-26 📝 Add documentation to the vectors module
2024-10-26 📝 Add documentation to the duration module
2024-10-26 📝 Add documentation to the measurement module
2024-10-26 📝 Add documentation to the utils module
2024-10-26 ✨ Make the firmware automatically reboot when needed by the OTA updater
2024-10-26 🧑‍💻 Implement the Debug trait for GCodeExecuter
2024-10-26 📝 Update the documentation of the library module
2024-10-26 🔥 Remove the log_in_isr module
2024-10-26 🎨 Format some code in the build file
2024-10-28 👷 Fix Github workflow to update firmware's documentation
2024-10-28 🐛 Update the name of an header in an API endpoint of the firmware
2024-10-28 🎉 Begin the Svelte control interface project
